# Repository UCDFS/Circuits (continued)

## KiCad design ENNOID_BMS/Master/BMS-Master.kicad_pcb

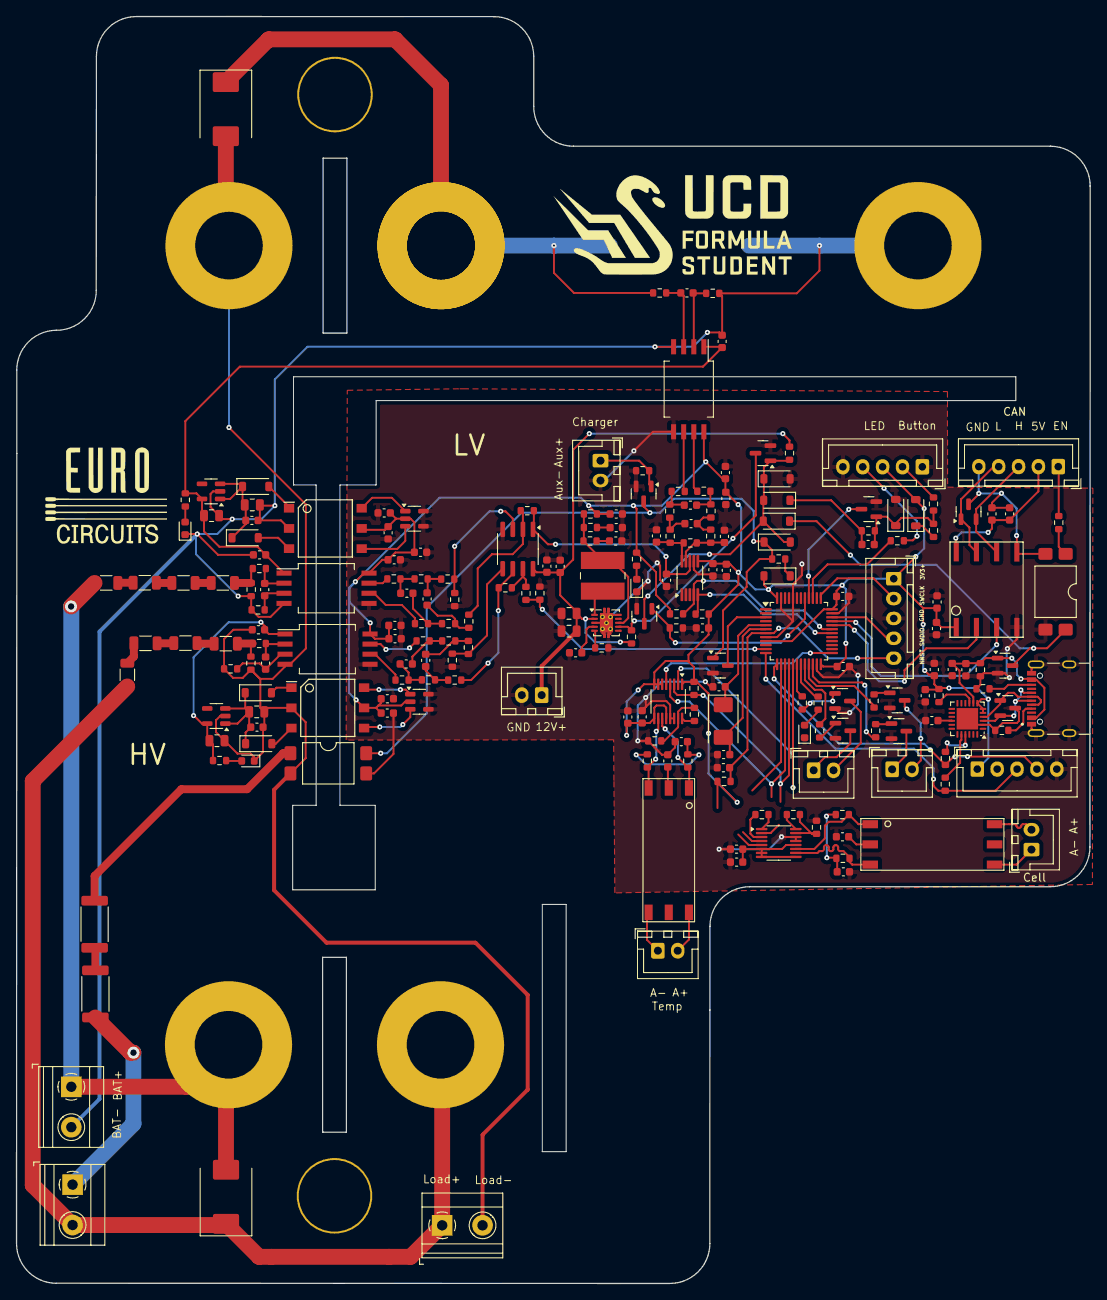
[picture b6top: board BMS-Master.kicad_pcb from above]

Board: 2 copper layers, 135.1 x 159.4 mm, 218 parts (1 on the bottom side), 149 nets.

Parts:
C1, C2, C5, C6: 10u; C_0805_2012Metric
C3, C4, C8, C10, C12, C13, C14, C15, C16, C17, C29, C30, C31, C32, C34, C44, C51, C52, C53, C54, C55, C56, C58, C60, C63, C65: 100n; C_0603_1608Metric
C7, C9, C11: 330p; C_0603_1608Metric
C18, C19, C20, C35, C57, C61: 2.2u; C_0603_1608Metric
C21, C22, C39, C40, C41: 10u; C_0603_1608Metric
C23, C24, C25: 2.2n; C_0603_1608Metric
C26, C27, C28: 220p; C_0603_1608Metric
C33, C49, C50, C62, C64: 1u; C_0603_1608Metric
C36, C37: 22u; C_0805_2012Metric
C38: 47n; C_0603_1608Metric
C42, C43: 18p; C_0603_1608Metric
C45, C46, C47, C48: 10n; C_0603_1608Metric
C59: 4.7u; C_0603_1608Metric
D1, D2: smcj440ca; D_SMC
D3, D5, D6: POWER; LED_0603_1608Metric
D4: STATUS; LED_0603_1608Metric
D7, D8, D9, D10: MBR0520; D_SOD-123
D11, D14: BZT52C16; D_SOD-123
D12, D13, D15, D16, D17: 1N4148W; D_SOD-123
D18: SP0502BAHT; SOT-23
D19: SZNUP2105L; SOT-23
J1: BAT_Power; Phoenix_1x2_1729128
J2: Contactor+; EVC500
J3: Contactor-; EVC500
J4: + 12V -; JST_XH_B2B-XH-A_1x02_P2.50mm_Vertical
J5: Power Button; JST_XH_B5B-XH-A_1x05_P2.50mm_Vertical
J6: INV_Power; Phoenix_1x2_1729128
J7: ISOSPI_CELL; JST_XH_B2B-XH-A_1x02_P2.50mm_Vertical
J8: ISOSPI_TEMP; JST_XH_B2B-XH-A_1x02_P2.50mm_Vertical
J9: Charger_Shutdown; JST_XH_B2B-XH-A_1x02_P2.50mm_Vertical
J10: LVE_Shutdown; JST_XH_B2B-XH-A_1x02_P2.50mm_Vertical
J11: CAN; JST_XH_B5B-XH-A_1x05_P2.50mm_Vertical
J13: Charge +; Phoenix_1x2_1729128
J14: Charger; JST_XH_B2B-XH-A_1x02_P2.50mm_Vertical
J15: DEBUG; JST_XH_B5B-XH-A_1x05_P2.50mm_Vertical
J16: SERIAL; JST_XH_B5B-XH-A_1x05_P2.50mm_Vertical
J17: UJ20-C-H-G-SMT-1-P16-TR; SAMESKY_UJ20-C-H-G-SMT-1-P16-TR
L1: 744043151; L_Wuerth_WE-PD2-Typ-MS
Q1, Q2, Q3, Q4, Q5, Q6, Q7, Q8, Q9, Q10: BSS138; SOT-23
R1, R2, R3, R6, R7: 470; R_0603_1608Metric
R4, R5: 5.1k; R_0603_1608Metric
R8, R9, R11, R12, R13, R14, R17, R18: 470K; R_1206_3216Metric
R10, R15: 220k; R_2512_6332Metric
R16: CSM2F-8518-L100J01
R19, R20, R21, R22, R23, R25, R33, R34, R35, R36, R37, R38, R47: 1k; R_0603_1608Metric
R24, R26, R81, R82, R83, R84: 10; R_0603_1608Metric
R27, R28, R29, R30, R31, R32, R55: 100; R_0603_1608Metric
R39, R40, R41, R42: 5.6k; R_0603_1608Metric
R43, R44, R52: 3.3k; R_0603_1608Metric
R45, R46, R48, R49: 33K; R_0603_1608Metric
R50, R53: 4.75k; R_0603_1608Metric
R51, R54, R56, R59, R61, R66, R80: 10k; R_0603_1608Metric
R57: 1M; R_0603_1608Metric
R58, R60: 4.7M; R_0603_1608Metric
R62: 130k; R_0603_1608Metric
R63, R64, R65: 1; R_0603_1608Metric
R67, R68: 806; R_0603_1608Metric
R69, R70, R71, R72: 51; R_0603_1608Metric
R73, R74: 1.2k; R_0603_1608Metric
R75, R76: 2k; R_0603_1608Metric
R77, R78: 240; R_0603_1608Metric
R79: 4.7k; R_0603_1608Metric
R85: 2.2k; R_0603_1608Metric
TR1, TR2: TRANSF5; WURTH-760390014
TR3, TR4: HM2108NL
U1, U2: TPS76350; SOT-23-5
U3, U4: AMC1301; SSO-8_6.8x5.9mm_Pitch1.27mm_Clearance8mm
U5, U17: SFH617A-2X009T; SMDIP-4_W9.53mm_Clearance8mm
U6: AMC1302; SSO-8_6.8x5.9mm_Pitch1.27mm_Clearance8mm
U7, U8: SN6501DBV; SOT-23-5
U9: OPA2197IDR; SOIC-8_3.9x4.9mm_P1.27mm
U10: ISL28022; MSOP-10_3x3mm_P0.5mm
U11: LM5165YDRC; Texas_S-PVSON-N10_ThermalVias
U12: STM32F303CCTx; LQFP-48_7x7mm_P0.5mm
U13, U14: LTC6820; MSOP-16_3x4.039mm_P0.5mm
U15: CP2104; QFN-24-1EP_4x4mm_P0.5mm_EP2.7x2.7mm
U16: ISO1050DUBR; ISO1050
Y1: 8MHz; Crystal_SMD_Abracon_ABM3-2Pin_5.0x3.2mm

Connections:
+3V3: C13.1, C14.1, C15.1, C16.1, C17.1, C18.1, C19.1, C20.1, C21.1, C22.1, C31.2, C41.2, C49.2, C50.2, C51.1, C52.1, C53.1, C54.1, C55.1, C56.1, C57.1, C58.1, C62.1, C63.1, D12.2 (A), D16.2 (A), J5.3, J15.1, J16.1, R2.2, R50.1, R53.1, R65.2, R66.1, R75.1, R76.1, R79.1, TR1.5, TR2.5, U3.8 (VDD2), U4.8 (VDD2), U6.8 (VDD2), U7.2 (VCC), U8.2 (VCC), U10.6 (Vs), U12.9 (VDDA), U12.24 (VDD), U12.36 (VDD), U12.48 (VDD), U13.1 (EN), U13.6 (Vcc0), U13.7 (POL), U13.8 (PHA), U13.9 (VCC), U13.12 (MSTR), U14.1 (EN), U14.6 (Vcc0), U14.7 (POL), U14.8 (PHA), U14.9 (VCC), U14.12 (MSTR), U15.5 (VIO), U15.6 (VDD), U15.7 (REGIN), U16.1 (Vcc1)
+12V: C33.1, C34.1, C36.2, C37.2, J4.1, R58.2, R60.2, U9.8 (V+), U11.2 (VIN)
/BAT+: D1.2 (A2), J1.1, J2.2, R8.1
/BMS_OK/Charge_enable: R81.1, U12.18 (PB0/ADC3_IN12/COMP4_INP/OPAMP2_VINP/OPA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)
/BMS_OK/Charge_enable_S: J9.2, Q7.3 (D)
/BMS_OK/Charger_Safety_S: J9.1, Q8.3 (D)
/BMS_OK/Charger_Safey: R82.1, U12.20 (PB2/ADC2_IN12/ADC3_EXTI2/ADC4_EXTI2/COM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)
/BMS_OK/Discharge_enable: R83.1, U12.21 (PB10/COMP5_INM/OPAMP3_VINM/OPAMP3_VINM_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)
/BMS_OK/Discharge_enable_S: J10.2, Q9.3 (D)
/BMS_OK/Multipurpose_enable: R84.1, U12.22 (PB11/ADC1_EXTI11/ADC2_EXTI11/COMP6_INP/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)
/BMS_OK/Multipurpose_enable_S: J10.1, Q10.3 (D)
/CAN/5V_CAN: C64.1, C65.2, J11.2, U16.8 (Vcc2)
/CAN/CANH: D19.2 (K), J11.3, U16.6 (CANL)
/CAN/CANL: D19.1 (K), J11.4, U16.7 (CANH)
/CAN/CAN_GND: C64.2, C65.1, D19.3 (A), J11.5, U16.5 (GND2), U17.2
/CAN/CAN_RX: U12.32 (ADC1_EXTI11/ADC2_EXTI11/CAN_RX/COMP1_OU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), U16.2 (RXD)
/CAN/CAN_TX: U12.33 (CAN_TX/COMP2_OUT/TIM16_CH1/TIM1_CH2N/TI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), U16.3 (TXD)
/CAN/EnableRequest: D15.1 (K), Q6.3 (D), U17.4
/CAN/Enable_CAN: J11.1, R85.1
/Load+: D1.1 (A1), J2.1, J6.1, J13.2, R9.1
/MCU/CS_CELL: U12.14 (ADC2_IN1/COMP1_INM/COMP2_INM/COMP3_INM/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), U13.5 (CSB)
/MCU/CS_TEMP: U12.25 (PB12/ADC4_IN3/COMP3_INM/I2C2_SMBA/I2S2_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), U14.5 (CSB)
/MCU/LED0: R3.2, U12.19 (PB1/ADC3_IN1/COMP4_OUT/OPAMP3_VOUT/TIM1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)
/MCU/MA_CELL: J7.1, TR3.6
/MCU/MA_TEMP: J8.1, TR4.6
/MCU/MISO: R75.2, R76.2, U12.16 (ADC2_IN3/COMP1_OUT/OPAMP2_VOUT/SPI1_MIS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), U13.3 (MISO), U14.3 (MISO)
/MCU/MOSI: U12.17 (ADC2_IN4/COMP2_INP/COMP2_OUT/OPAMP1_VIN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), U13.2 (MOSI), U14.2 (MOSI)
/MCU/NRST: C44.1, J15.5, R66.2, U12.7 (NRST)
/MCU/PA_CELL: J7.2, TR3.4
/MCU/PA_TEMP: J8.2, TR4.4
/MCU/PowerButton: Q2.3 (D), U12.40 (PB4/I2S3_ext_SD/SPI1_MISO/SPI3_MISO/SYS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)
/MCU/PowerEnable: Q3.1 (G), R59.1, U12.41 (PB5/I2C1_SMBA/I2S3_SD/SPI1_MOSI/SPI3_MO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)
/MCU/PowerLED: R1.2, U12.39 (PB3/I2S3_CK/SPI1_SCK/SPI3_SCK/SYS_JTDO-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)
/MCU/RX_USB: J16.4, R77.2, U12.13 (ADC1_IN4/COMP2_INP/OPAMP1_VINM/OPAMP1_V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)
/MCU/SCK: U12.15 (ADC2_IN2/COMP1_INM/COMP2_INM/COMP3_INM/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), U13.4 (SCK), U14.4 (SCK)
/MCU/SCL: R50.2, U10.5 (SCL), U12.30 (COMP5_OUT/DAC_EXTI9/I2C2_SCL/I2S3_MCK/T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)
/MCU/SDA: R53.2, U10.4 (SDA), U12.31 (COMP6_OUT/I2C2_SDA/TIM17_BKIN/TIM1_CH3/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)
/MCU/SWCLK: J15.2, U12.37 (I2C1_SDA/SYS_JTCK-SWCLK/TIM1_BKIN/TIM8_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)
/MCU/SWDIO: J15.4, U12.34 (IR_OUT/SYS_JTMS-SWDIO/TIM16_CH1N/TIM4_C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)
/MCU/TX_USB: J16.3, R78.2, U12.12 (ADC1_IN3/ADC3_EXTI2/ADC4_EXTI2/COMP2_IN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)
/MCU/Vpack: R51.2, R52.1, U12.11 (ADC1_IN2/COMP1_INP/OPAMP1_VINP/OPAMP1_V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)
/PowerMonitor/Current: D2.1 (A1), J3.1, R16.2, R22.1
/PowerMonitor/ISO+5V: C1.1, C8.1, C12.1, R6.2, U1.5 (VOUT), U3.1 (VDD1), U6.1 (VDD1)
/PowerMonitor/ISO+5V_LOAD: C2.1, C10.1, R7.2, U2.5 (VOUT), U4.1 (VDD1)
/PowerMonitor/Vbat: C29.1, R48.2, U9.1, U10.8 (Vbus)
/PowerSupply/ChargeDetect: D17.1 (K), Q1.3 (D), Q5.1 (G), R61.2, U5.4
/PowerSupply/PushButton: J5.2, R55.1
/USB/D+: D18.2 (K), J17.A6 (DP1), J17.B6 (DP2), U15.3 (D+)
/USB/D-: D18.1 (K), J17.A7 (DN1), J17.B7 (DN2), U15.4 (D-)
/USB/Vusb: C60.1, C61.1, J17.A4_B9 (VBUS), J17.B4_A9 (VBUS), Q6.1 (G), R80.1, U15.8 (VBUS)
GND: C13.2, C14.2, C15.2, C16.2, C17.2, C18.2, C19.2, C20.2, C21.2, C22.2, C29.2, C30.1, C31.1, C32.1, C33.2, C34.2, C36.1, C37.1, C38.1, C39.1, C40.1, C41.1, C42.2, C43.2, C44.2, C45.2, C46.2, C47.1, C48.1, C49.1, C50.1, C51.2, C52.2, C53.2, C54.2, C55.2, C56.2, C57.2, C58.2, C59.2, C60.2, C61.2, C62.2, C63.2, D3.1 (K), D4.1 (K), D11.2 (A), D14.2 (A), D18.3 (A), J4.2, J5.1, J5.5, J14.2, J15.3, J16.5, J17.A1_B12 (GND), J17.B1_A12 (GND), J17.SH1 (SHIELD), J17.SH2 (SHIELD), J17.SH3 (SHIELD), J17.SH4 (SHIELD), Q1.2 (S), Q2.2 (S), Q3.2 (S), Q4.2 (S), Q5.2 (S), Q6.2 (S), Q7.2 (S), Q8.2 (S), Q9.2 (S), Q10.2 (S), R4.2, R5.2, R45.2, R46.2, R52.2, R54.2, R59.2, R62.1, R67.2, R68.2, R80.2, U3.5 (GND2), U4.5 (GND2), U5.3, U6.5 (GND2), U7.4 (GND), U7.5 (GND), U8.4 (GND), U8.5 (GND), U9.4 (V-), U10.7 (GND), U11.3 (ILIM), U11.10 (GND), U11.11 (PAD), U12.8 (VSSA), U12.23 (VSS), U12.35 (VSS), U12.44 (BOOT0), U12.47 (VSS), U13.13 (SLOW), U13.14 (GND), U14.13 (SLOW), U14.14 (GND), U15.2 (GND), U15.25 (GND), U16.4 (GND1), U17.3
GNDA: C1.2, C3.2, C5.2, C8.2, C12.2, D5.1 (K), J1.2, R16.1, R19.2, R21.1, R23.2, TR1.2, U1.2 (GND), U3.4 (GND2), U6.4 (GND2)
GNDREF: C2.2, C4.2, C6.2, C10.2, D2.2 (A2), D6.1 (K), J3.2, J6.2, R20.2, R25.2, TR2.2, U2.2 (GND), U4.4 (GND2), U5.2
unnamed: C23.1, R27.1, R33.1
unnamed: C23.2, R28.1, R34.1
unnamed: C24.1, R29.1, R35.1
unnamed: C24.2, R30.1, R36.1
unnamed: C25.1, R31.1, R37.1
unnamed: C25.2, R32.1, R38.1
unnamed: C26.1, R33.2, R43.2
unnamed: C26.2, R34.2, R44.2
unnamed: C27.1, R35.2, R39.1
unnamed: C27.2, R36.2, R40.1
unnamed: C28.1, R37.2, R41.1
unnamed: C28.2, R38.2, R42.1
unnamed: C39.2, R63.2
unnamed: C40.2, R64.2
unnamed: C45.1, TR3.2
unnamed: C46.1, TR4.2
unnamed: C47.2, R69.1, R70.2
unnamed: C48.2, R71.1, R72.2
unnamed: D3.2 (A), R2.1
unnamed: D4.2 (A), R3.1
unnamed: D5.2 (A), R6.1
unnamed: D6.2 (A), R7.1
unnamed: D7.2 (A), TR1.1
unnamed: C3.1, C5.1, D7.1 (K), D8.1 (K), U1.1 (VIN), U1.3 (EN)
unnamed: D8.2 (A), TR1.3
unnamed: D9.2 (A), TR2.1
unnamed: D10.2 (A), TR2.3
unnamed: C4.1, C6.1, D9.1 (K), D10.1 (K), U2.1 (VIN), U2.3 (EN)
unnamed: C35.1, D11.1 (K), Q2.1 (G), R55.2, R56.1, R57.1
unnamed: D12.1 (K), R56.2
unnamed: D13.2 (A), D14.1 (K), D15.2 (A), D17.2 (A), Q3.3 (D), Q4.1 (G), R58.1
unnamed: C35.2, D13.1 (K), R57.2
unnamed: D16.1 (K), R61.1
unnamed: J5.4, R1.1
unnamed: J13.1, R10.2
unnamed: J14.1, Q1.1 (G), R54.1
unnamed: J17.A5 (CC1), R5.1
unnamed: J17.B5 (CC2), R4.1
unnamed: Q4.3 (D), R60.1, U11.7 (EN)
unnamed: Q5.3 (D), U12.3 (PC14/RCC_OSC32_IN)
unnamed: Q7.1 (G), R81.2
unnamed: Q8.1 (G), R82.2
unnamed: Q9.1 (G), R83.2
unnamed: Q10.1 (G), R84.2
unnamed: R10.1, R15.2
unnamed: R8.2, R11.1
unnamed: R11.2, R13.1
unnamed: R9.2, R12.1
unnamed: R12.2, R14.1
unnamed: R13.2, R17.1
unnamed: R14.2, R18.1
unnamed: R15.1, U5.1
unnamed: R17.2, R19.1, R26.1
unnamed: R18.2, R20.1, R24.1
unnamed: R49.2, R51.1, U9.7
unnamed: R85.2, U17.1
unnamed: C9.2, R23.1, U3.3 (VINN)
unnamed: C9.1, R26.2, U3.2 (VINP)
unnamed: R29.2, U3.6 (VOUTN)
unnamed: R30.2, U3.7 (VOUTP)
unnamed: C11.2, R25.1, U4.3 (VINN)
unnamed: C11.1, R24.2, U4.2 (VINP)
unnamed: R31.2, U4.6 (VOUTN)
unnamed: R32.2, U4.7 (VOUTP)
unnamed: C7.2, R22.2, U6.3 (VINN)
unnamed: C7.1, R21.2, U6.2 (VINP)
unnamed: R27.2, U6.6 (VOUTN)
unnamed: R28.2, U6.7 (VOUTP)
unnamed: TR1.6, U7.1 (D1)
unnamed: TR1.4, U7.3 (D2)
unnamed: TR2.6, U8.1 (D1)
unnamed: TR2.4, U8.3 (D2)
unnamed: R40.2, R45.1, U9.3 (+)
unnamed: R39.2, R48.1, U9.2 (-)
unnamed: R42.2, R46.1, U9.5 (+)
unnamed: R41.2, R49.1, U9.6 (-)
unnamed: C30.2, R43.1, R47.1, U10.10 (Vin+)
unnamed: C32.2, R44.1, R47.2, U10.9 (Vin-)
unnamed: L1.2, R63.1, R64.1, R65.1, U11.8 (FB)
unnamed: R62.2, U11.5 (RT)
unnamed: C38.2, U11.4 (SS)
unnamed: L1.1, U11.1 (SW)
unnamed: C42.1, U12.5 (PF0/I2C2_SDA/RCC_OSC_IN/TIM1_CH3N), Y1.1
unnamed: C43.1, U12.6 (PF1/I2C2_SCL/RCC_OSC_OUT), Y1.2
unnamed: R73.1, U13.16 (IBIAS)
unnamed: R67.1, R73.2, U13.15 (ICMP)
unnamed: R70.1, TR3.3, U13.10 (IM)
unnamed: R69.2, TR3.1, U13.11 (IP)
unnamed: R74.1, U14.16 (IBIAS)
unnamed: R68.1, R74.2, U14.15 (ICMP)
unnamed: R72.1, TR4.3, U14.10 (IM)
unnamed: R71.2, TR4.1, U14.11 (IP)
unnamed: R78.1, U15.20 (RXD)
unnamed: R77.1, U15.21 (TXD)
unnamed: C59.1, U15.16 (VPP)
unnamed: R79.2, U15.9 (~RST)

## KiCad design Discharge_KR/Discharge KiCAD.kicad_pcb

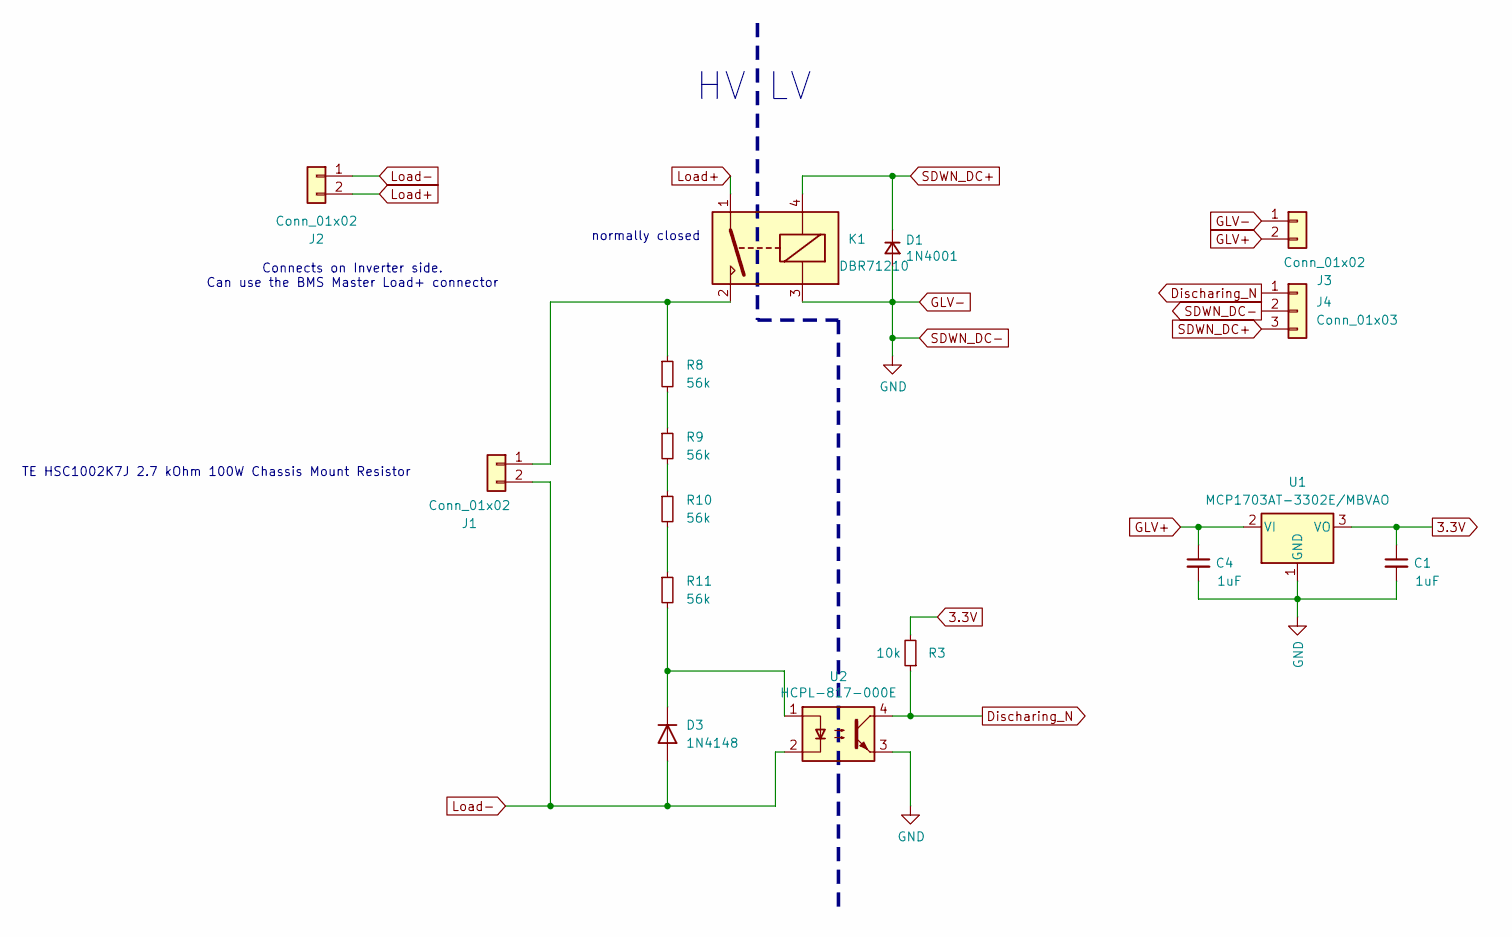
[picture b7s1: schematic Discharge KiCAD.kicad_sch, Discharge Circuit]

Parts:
C1, C4: 1uF; FA18X7R1H104KNU00; Part Number FA18X7R1E105KRU00
D1: 1N4001; D_DO-41_SOD81_P10.16mm_Horizontal; Part Number 1N4001
D3: 1N4148; D_DO-35_SOD27_P7.62mm_Horizontal; Part Number 1N4148
J1, J2: Conn_01x02; Phoenix_1x2_1729128; Part Number 1729128
J3: Conn_01x02; JST_XH_B2B-XH-A_1x02_P2.50mm_Vertical; Part Number B2B-XH-A
J4: Conn_01x03; JST_XH_B3B-XH-A_1x03_P2.50mm_Vertical; Part Number B3B-XH-A
K1: DBR71210; Part Number DBR71210
R3: 10k; R_Axial_DIN0207_L6.3mm_D2.5mm_P10.16mm_Horizontal; Part Number MCF 0.25W 10K
R8, R9, R10, R11: 56k; R_Axial_DIN0207_L6.3mm_D2.5mm_P10.16mm_Horizontal; Part Number MCF 0.25W 56K
U1: MCP1703AT-3302E/MBVAO; SOT-89-3; Part Number MCP1703AT-3302E/MBVAO
U2: HCPL-817-000E; DIP-4_W7.62mm; Part Number HCPL-817-000E

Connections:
3.3V: C1.1, R3.2, U1.3 (VO)
Discharing_N: J4.1, R3.1, U2.4
GLV+: C4.1, J3.2, U1.2 (VI)
GLV-: C1.2, C4.2, D1.2 (A), J3.1, J4.2, K1.3, U1.1 (GND), U2.3
Load+: J2.2, K1.1
Load-: D3.2 (A), J1.2, J2.1, U2.2
unnamed: D3.1 (K), R11.2, U2.1
unnamed: J1.1, K1.2, R8.1
unnamed: R8.2, R9.1
unnamed: R9.2, R10.1
unnamed: R10.2, R11.1
SDWN_DC+: D1.1 (K), J4.3, K1.4

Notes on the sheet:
normally closed
TE HSC1002K7J 2.7 kOhm 100W Chassis Mount Resistor
Connects on Inverter side. Can use the BMS Master Load+ connector
HV LV

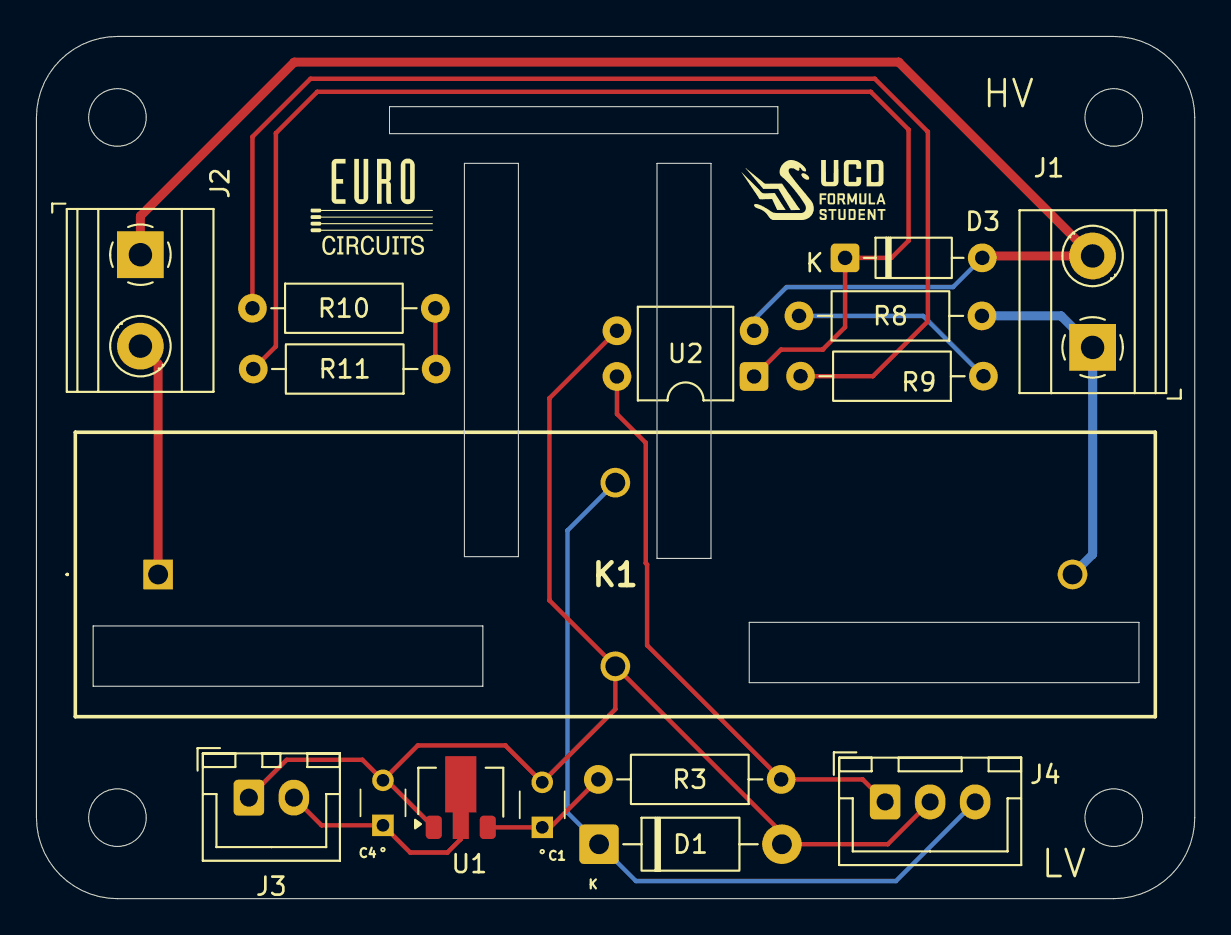
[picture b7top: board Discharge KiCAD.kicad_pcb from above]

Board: 2 copper layers, 64.3 x 47.9 mm, 16 parts (0 on the bottom side), 12 nets.

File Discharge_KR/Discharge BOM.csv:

"Reference","Value","Part Number","Datasheet","Footprint","Qty","DNP"
"U2","HCPL-817-000E","HCPL-817-000E","https://www.mouser.ie/datasheet/2/678/AV02_0265EN_2021_04_26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","Package_DIP:DIP-4_W7.62mm","1",""
"U1","MCP1703AT-3302E/MBVAO","MCP1703AT-3302E/MBVAO","http://ww1.microchip.com/downloads/en/DeviceDoc/20005122B.pdf","Package_TO_SOT_SMD:SOT-89-3","1",""
"R8,R9,R10,R11","56k","MCF 0.25W 56K","https://www.farnell.com/datasheets/3436052.pdf?_gl=1*1pxxutc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","Resistor_THT:R_Axial_DIN0207_L6.3mm_D2.5mm_P10.16mm_Horizontal","4",""
"R3","10k","MCF 0.25W 10K","https://www.farnell.com/datasheets/3436052.pdf?_gl=1*1pxxutc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","Resistor_THT:R_Axial_DIN0207_L6.3mm_D2.5mm_P10.16mm_Horizontal","1",""
"K1","DBR71210","DBR71210","https://www.mouser.ie/datasheet/2/657/cynergy3_d_pcb_v2-1892244.pdf","DBR71210:DBR71210","1",""
"J4","Conn_01x03","B3B-XH-A","https://www.jst-mfg.com/product/pdf/eng/eXH.pdf","Connector_JST:JST_XH_B3B-XH-A_1x03_P2.50mm_Vertical","1",""
"J1,J2,J3","Conn_01x02","1729128,B2B-XH-A","https://www.phoenixcontact.com/en-us/products/printed-circui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","Connector_JST:JST_XH_B2B-XH-A_1x02_P2.50mm_Vertical,Phoenix 1x2 Connector:Phoenix_1x2_1729128","3",""
"D3","1N4148","1N4148","https://www.mouser.ie/datasheet/3/101/1/1N914-D.PDF","Diode_THT:D_DO-35_SOD27_P7.62mm_Horizontal","1",""
"D1","1N4001","1N4001","http://www.vishay.com/docs/88503/1n4001.pdf","Diode_THT:D_DO-41_SOD81_P10.16mm_Horizontal","1",""
"C1,C4","1uF","FA18X7R1E105KRU00","http://www.farnell.com/datasheets/2923220.pdf","FA14_Capacitor:FA18X7R1H104KNU00","2",""

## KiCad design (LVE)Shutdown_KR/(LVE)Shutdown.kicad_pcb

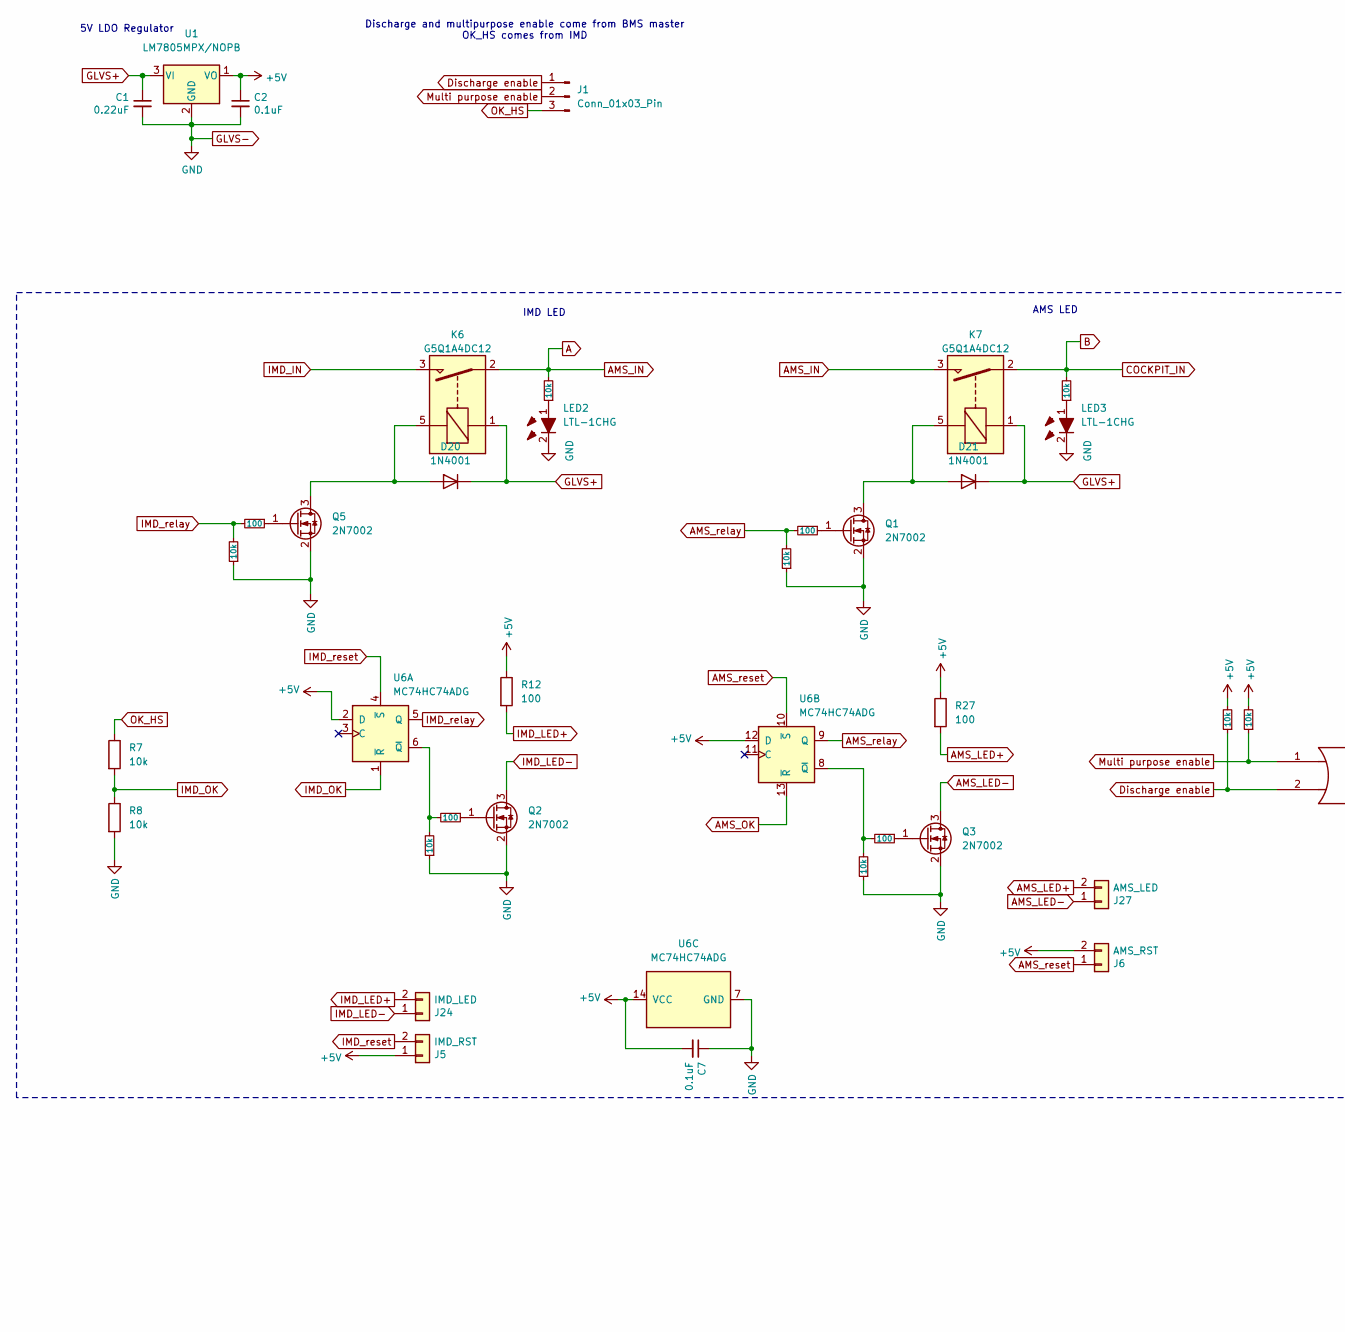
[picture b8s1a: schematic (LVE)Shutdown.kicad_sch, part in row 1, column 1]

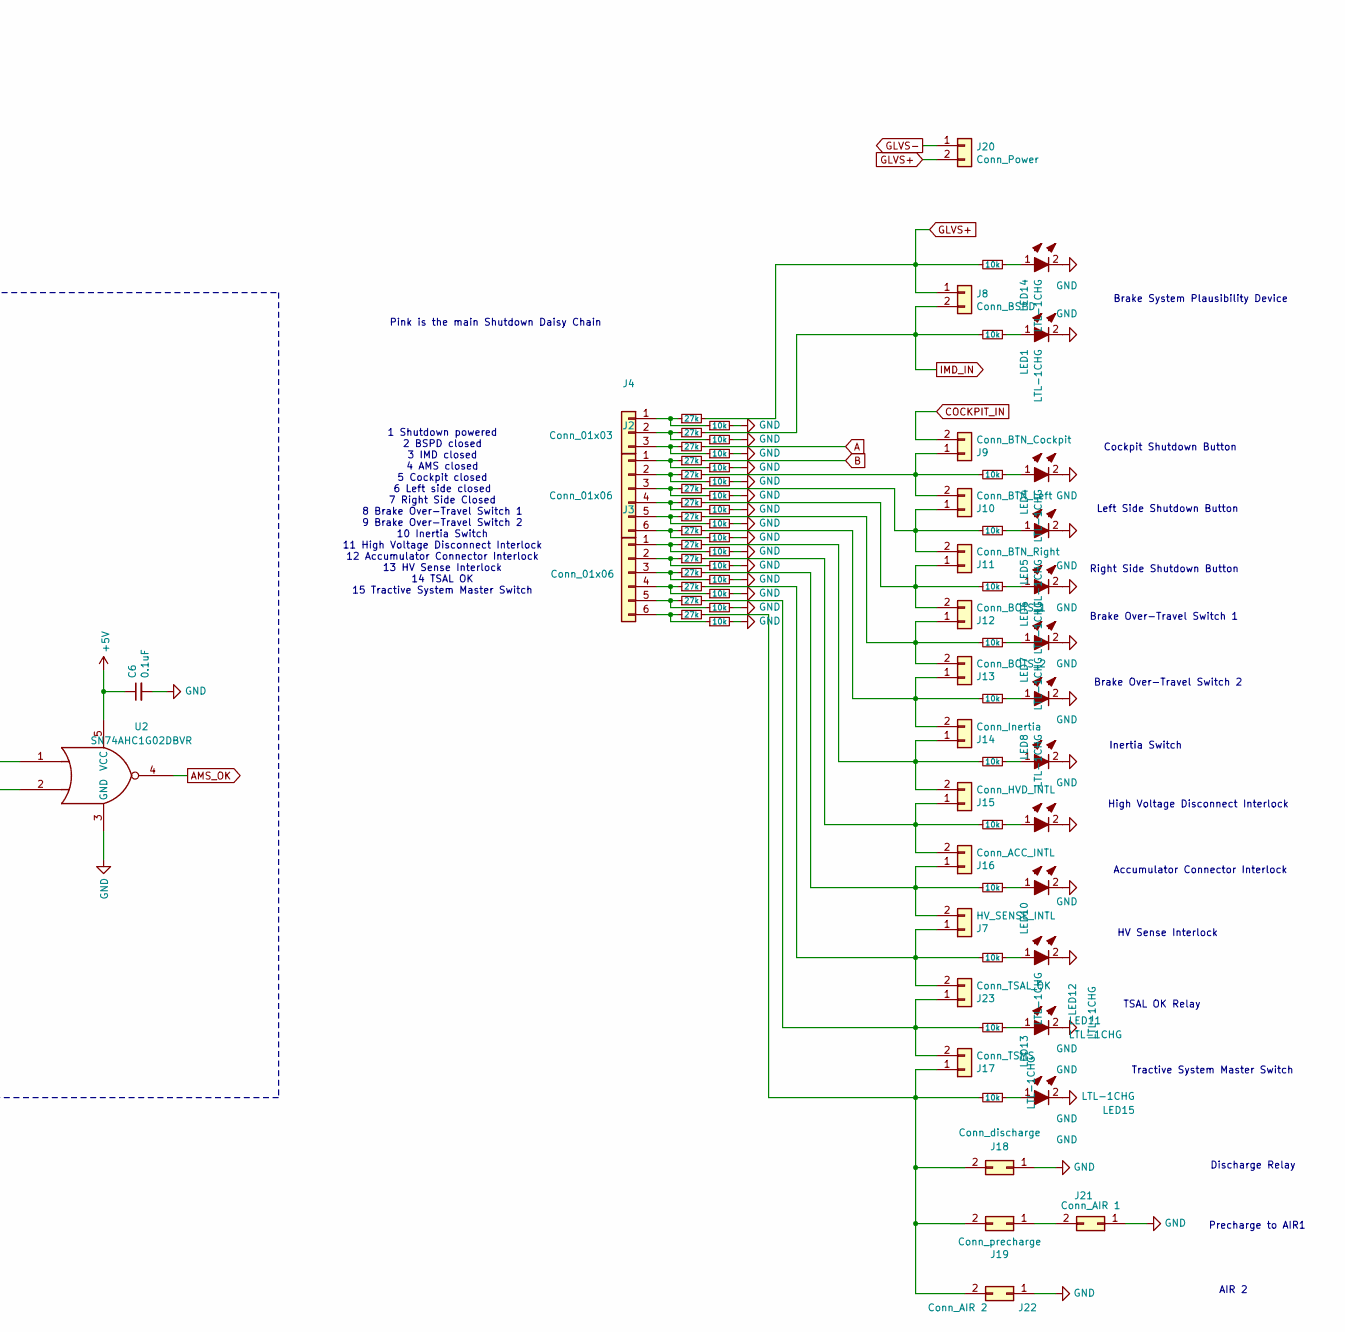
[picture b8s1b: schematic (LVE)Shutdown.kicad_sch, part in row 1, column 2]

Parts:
C1: 0.22uF; FA14X7R1H224KNU00; Part Number FA14X7R1H224KNU00
C2, C6, C7: 0.1uF; FA18X7R1H104KNU00; Part Number FA18X7R1H104KNU00
D20, D21: 1N4001; D_DO-41_SOD81_P10.16mm_Horizontal; Part Number 1n4001
J1: Conn_01x03_Pin; JST_XH_B3B-XH-A_1x03_P2.50mm_Vertical; Part Number B3B-XH-A
J2, J3: Conn_01x06; JST_XH_B6B-XH-A_1x06_P2.50mm_Vertical; Part Number B6B-XH-A
J4: Conn_01x03; JST_XH_B3B-XH-A_1x03_P2.50mm_Vertical; Part Number B3B-XH-A
J5: IMD_RST; JST_XH_B2B-XH-A_1x02_P2.50mm_Vertical; Part Number B2B-XH-A
J6: AMS_RST; JST_XH_B2B-XH-A_1x02_P2.50mm_Vertical; Part Number B2B-XH-A
J7: HV_SENSE_INTL; JST_XH_B2B-XH-A_1x02_P2.50mm_Vertical; Part Number B2B-XH-A
J8: Conn_BSPD; JST_XH_B2B-XH-A_1x02_P2.50mm_Vertical; Part Number B2B-XH-A
J9: Conn_BTN_Cockpit; JST_XH_B2B-XH-A_1x02_P2.50mm_Vertical; Part Number B2B-XH-A
J10: Conn_BTN_Left; JST_XH_B2B-XH-A_1x02_P2.50mm_Vertical; Part Number B2B-XH-A
J11: Conn_BTN_Right; JST_XH_B2B-XH-A_1x02_P2.50mm_Vertical; Part Number B2B-XH-A
J12: Conn_BOTS_1; JST_XH_B2B-XH-A_1x02_P2.50mm_Vertical; Part Number B2B-XH-A
J13: Conn_BOTS_2; JST_XH_B2B-XH-A_1x02_P2.50mm_Vertical; Part Number B2B-XH-A
J14: Conn_Inertia; JST_XH_B2B-XH-A_1x02_P2.50mm_Vertical; Part Number B2B-XH-A
J15: Conn_HVD_INTL; JST_XH_B2B-XH-A_1x02_P2.50mm_Vertical; Part Number B2B-XH-A
J16: Conn_ACC_INTL; JST_XH_B2B-XH-A_1x02_P2.50mm_Vertical; Part Number B2B-XH-A
J17: Conn_TSMS; JST_XH_B2B-XH-A_1x02_P2.50mm_Vertical; Part Number B2B-XH-A
J18: Conn_discharge; JST_XH_B2B-XH-A_1x02_P2.50mm_Vertical; Part Number B2B-XH-A
J19: Conn_precharge; JST_XH_B2B-XH-A_1x02_P2.50mm_Vertical; Part Number B2B-XH-A
J20: Conn_Power; JST_XH_B2B-XH-A_1x02_P2.50mm_Vertical; Part Number B2B-XH-A
J21: Conn_AIR 1; JST_XH_B2B-XH-A_1x02_P2.50mm_Vertical; Part Number B2B-XH-A
J22: Conn_AIR 2; JST_XH_B2B-XH-A_1x02_P2.50mm_Vertical; Part Number B2B-XH-A
J23: Conn_TSAL_OK; JST_XH_B2B-XH-A_1x02_P2.50mm_Vertical; Part Number B2B-XH-A
J24: IMD_LED; JST_XH_B2B-XH-A_1x02_P2.50mm_Vertical; Part Number B2B-XH-A
J27: AMS_LED; JST_XH_B2B-XH-A_1x02_P2.50mm_Vertical; Part Number B2B-XH-A
K6, K7: G5Q1A4DC12; Relay_SPST_Omron-G5Q-1A; Part Number G5Q1A4DC12
LED1, LED2, LED3, LED4, LED5, LED6, LED7, LED8, LED9, LED10, LED11, LED12, LED13, LED14, LED15: LTL-1CHG; LTL1CHG; Mouser Part Number 859-LTL-1CHG
Q1, Q2, Q3, Q5: 2N7002; SOT-23; Part Number 2N7002
R1, R2, R3, R16, R17, R18, R19, R20, R21, R22, R23, R24, R25, R29, R53: 27k; R_Axial_DIN0207_L6.3mm_D2.5mm_P10.16mm_Horizontal; Part Number MCF 0.25W 27K
R4, R5, R6, R7, R8, R9, R10, R11, R13, R15, R28, R30, R31, R32, R33, R34, R35, R36, R37, R38, R39, R40, R41, R42, R43, R44, R45, R46, R47, R48, R49, R50, R52, R54, R55, R57, R59, R60: 10k; R_Axial_DIN0207_L6.3mm_D2.5mm_P10.16mm_Horizontal; Part Number MCF 0.25W 10K
R12, R14, R26, R27, R56, R58: 100; R_Axial_DIN0207_L6.3mm_D2.5mm_P10.16mm_Horizontal; Part Number MCF 0.25W 100
U1: LM7805MPX/NOPB; SOT-223-3_TabPin2; Part Number LM7805MPX/NOPB
U2: SN74AHC1G02DBVR; SOT-23-5; Part Number SN74AHC1G02DBVR
U6: MC74HC74ADG; SOIC-14_3.9x8.7mm_P1.27mm; Part Number MC74HC74ADG

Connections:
+5V: C2.1, C6.1, C7.2, J5.1, J6.2, R10.2, R11.2, R12.1, R27.1, U1.1 (VO), U2.5 (VCC), U6.2 (D), U6.12 (D), U6.14 (VCC)
A: K6.2, K7.3, R3.2, R60.2
AMS_LED+: J27.2, R27.2
AMS_LED-: J27.1, Q3.3 (D)
AMS_OK: U2.4, U6.13 (~R)
AMS_relay: R57.2, R58.2, U6.9 (Q)
AMS_reset: J6.1, U6.10 (~S)
B: J9.2, K7.2, R9.2, R16.2
Discharge enable: J1.1, R10.1, U2.2
GLVS+: C1.1, D20.1 (K), D21.1 (K), J8.1, J20.2, K6.1, K7.1, R1.2, R40.2, U1.3 (VI)
GLVS-: C1.2, C2.2, C6.2, C7.1, J18.1, J20.1, J21.1, J22.1, LED1.2 (K), LED2.2 (K), LED3.2 (K), LED4.2 (K), LED5.2 (K), LED6.2 (K), LED7.2 (K), LED8.2 (K), LED9.2 (K), LED10.2 (K), LED11.2 (K), LED12.2 (K), LED13.2 (K), LED14.2 (K), LED15.2 (K), Q1.2 (S), Q2.2 (S), Q3.2 (S), Q5.2 (S), R4.2, R5.2, R6.2, R8.2, R13.1, R15.1, R30.2, R31.2, R32.2, R33.2, R34.2, R35.2, R36.2, R37.2, R38.2, R39.2, R41.2, R54.2, R55.1, R57.1, U1.2 (GND), U2.3 (GND), U6.7 (GND)
IMD_IN: J8.2, K6.3, R2.2, R59.2
IMD_LED+: J24.2, R12.2
IMD_LED-: J24.1, Q2.3 (D)
IMD_OK: R7.2, R8.1, U6.1 (~R)
IMD_relay: R55.2, R56.2, U6.5 (Q)
IMD_reset: J5.2, U6.4 (~S)
Multi purpose enable: J1.2, R11.1, U2.1
unnamed: D20.2 (A), K6.5, Q5.3 (D)
unnamed: D21.2 (A), K7.5, Q1.3 (D)
unnamed: J2.1, R16.1, R30.1
unnamed: J2.2, R17.1, R31.1
unnamed: J2.3, R18.1, R32.1
unnamed: J2.4, R19.1, R33.1
unnamed: J2.5, R20.1, R34.1
unnamed: J2.6, R21.1, R35.1
unnamed: J3.1, R22.1, R36.1
unnamed: J3.2, R23.1, R37.1
unnamed: J3.3, R24.1, R38.1
unnamed: J3.4, R25.1, R39.1
unnamed: J3.5, R53.1, R54.1
unnamed: J3.6, R29.1, R41.1
unnamed: J4.1, R1.1, R4.1
unnamed: J4.2, R2.1, R5.1
unnamed: J4.3, R3.1, R6.1
unnamed: J10.1, J11.2, R18.2, R43.2
unnamed: J9.1, J10.2, R17.2, R42.2
unnamed: J11.1, J12.2, R19.2, R44.2
unnamed: J12.1, J13.2, R20.2, R45.2
unnamed: J13.1, J14.2, R21.2, R46.2
unnamed: J14.1, J15.2, R22.2, R47.2
unnamed: J15.1, J16.2, R23.2, R48.2
unnamed: J7.2, J16.1, R24.2, R49.2
unnamed: J17.1, J18.2, J19.2, J22.2, R29.2, R52.2
unnamed: J17.2, J23.1, R50.2, R53.2
unnamed: J19.1, J21.2
unnamed: J7.1, J23.2, R25.2, R28.2
unnamed: LED1.1 (A), R59.1
unnamed: LED2.1 (A), R60.1
unnamed: LED3.1 (A), R9.1
unnamed: LED4.1 (A), R42.1
unnamed: LED5.1 (A), R43.1
unnamed: LED6.1 (A), R44.1
unnamed: LED7.1 (A), R45.1
unnamed: LED8.1 (A), R46.1
unnamed: LED9.1 (A), R47.1
unnamed: LED10.1 (A), R48.1
unnamed: LED11.1 (A), R52.1
unnamed: LED12.1 (A), R50.1
unnamed: LED13.1 (A), R49.1
unnamed: LED14.1 (A), R40.1
unnamed: LED15.1 (A), R28.1
unnamed: Q1.1 (G), R58.1
unnamed: Q2.1 (G), R14.1
unnamed: Q3.1 (G), R26.1
unnamed: Q5.1 (G), R56.1
unnamed: R13.2, R14.2, U6.6 (~Q)
unnamed: R15.2, R26.2, U6.8 (~Q)
OK_HS: J1.3, R7.1

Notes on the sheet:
HV Sense Interlock
Discharge and multipurpose enable come from BMS master OK_HS comes from IMD
Pink is the main Shutdown Daisy Chain
Accumulator Connector Interlock
Right Side Shutdown Button
Brake System Plausibility Device
Left Side Shutdown Button
Brake Over-Travel Switch 1
Precharge to AIR1
Discharge Relay
Cockpit Shutdown Button
Inertia Switch
IMD LED
Brake Over-Travel Switch 2
Tractive System Master Switch
1 Shutdown powered 2 BSPD closed 3 IMD closed 4 AMS closed 5 Cockpit closed 6 Left side closed 7 Right Side Closed 8 Brake Over-Travel Switch 1 9 Brake Over-Travel Switch 2 10 Inertia Switch 11 High Voltage Disconnect Interlock 12 Accumulator Connector Interlock 13 HV Sense Interlock 14 TSAL OK 15 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
AMS LED
High Voltage Disconnect Interlock
AIR 2
TSAL OK Relay
5V LDO Regulator
